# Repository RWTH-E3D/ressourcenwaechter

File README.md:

# Ressourcenwächter

*Resource Guardian - An open-source, modular Indoor Environmental Quality (IEQ) monitoring system featuring a gamified Graphical User Interface (GUI)*

**Resource Guardian's Wiki: [Link](https://rw.e3d.rwth-aachen.de/en/homepage-en/)**

## Overview

<!-- TOC -->
- [Ressourcenwächter](#ressourcenwächter)
  - [Overview](#overview)
  - [Key Features](#key-features)
  - [Design](#design)
  - [DIY Guide](#diy-guide)
  - [License](#license)
    - [Software \& Firmware](#software--firmware)
    - [Hardware](#hardware)
    - [Feedback System (Texts \& Concepts)](#feedback-system-texts--concepts)
    - [Documentation](#documentation)
    - [Artworks](#artworks)
  - [Acknowledgements](#acknowledgements)
  - [How to cite](#how-to-cite)
  - [Contributors](#contributors)
<!-- TOC -->

## Key Features

- **Modular IEQ monitoring system**

  Open-source system for monitoring key IEQ parameters, designed for real-world field studies and long-term deployment.

- **Multi-sensor data acquisition**

  Support for air temperature, humidity, illuminance, sound level, CO<sub>2</sub> concentration, VOC, wind speed, window status, electric power, and other IEQ sensors, with synchronized data collection and time-stamping.

- **Autonomous system**

  On-device GUI providing real-time visualization, intuitive interaction, and immediate feedback without requiring an external computer or internet connection. All data are stored locally on a microSD card.

- **Behavior-oriented feedback system**

  Context-aware feedback and recommendations aiming to support more resource-/energy-efficient and healthy user behavior, based on measured IEQ conditions.

<table>
<tr>
  <td align="center" valign="top">
      
      <br/>
      <sub><strong>Feedback System</strong><br/>Resource Guardian can provide recommendations and energy-saving tips based on your current IEQ environment</sub>
  </td>
  <td align="center" valign="top">
      
      <br/>
      <sub><strong>Sensor Data</strong><br/>Resource Guardian's modular design allows real-time IEQ data to be displayed based on your sensor configuration.</sub>
  </td>
</tr>
</table>

## Design

1. [Hardware](./hardware)
   1. [Enclosure](./hardware/enclosure)
   2. [PCB](./hardware/pcb)
2. [Microcontroller Firmware](./firmware)
3. [GUI](./software/gui)

## DIY Guide

- Step 1: [Prepare enclosure](https://rw.e3d.rwth-aachen.de/en/wiki/prepare-enclosure/)
- Step 2: [Prepare PCB](https://rw.e3d.rwth-aachen.de/en/wiki/prepare-pcb/)
- Step 3: [Assembling Resource Guardian](https://rw.e3d.rwth-aachen.de/en/wiki/assembling-ressourcenwaechter/)

## License

The *Ressourcenwächter (Resource Guardian)* project is a mixed open-source project consisting of software, firmware, hardware designs, documentation, feedback content, and third-party artwork. Different components of the project are released under different licenses, as outlined below.

In general, this project may be used, modified, and redistributed, provided that appropriate attribution is given and the respective license terms of each component are respected. **Non-commercial** use is permitted for all components, while commercial use is restricted for parts of the project licensed under non-commercial Creative Commons licenses. Third-party assets remain subject to their original licenses.

Please read this section carefully before reusing or redistributing any part of the project.

### Software & Firmware

The codebase is structured into following main components:

1. **Firmware:** Code running on embedded microcontrollers.

2. **Software for touch display GUI:** Graphical user interface running directly on the monitoring device.

<!-- 3. **Desktop software:** Desktop applications running on computers. -->

Author: Qirui Huang

License: GNU General Public License v3.0 (GPL-3.0)

Unless stated otherwise, all software and firmware developed within this project are licensed under GPL-3.0. Any derivative work must be distributed under the same license.

### Hardware

Author: Qirui Huang

License: Creative Commons Attribution-NonCommercial-ShareAlike
4.0 International (CC BY-NC-SA 4.0)

This license applies to all hardware-related materials, including but not limited to schematics, PCB layouts, enclosure designs, and mechanical drawings.

Commercial use is not permitted. Adaptations must be shared under the same
license.

### Feedback System (Texts & Concepts)

Authors: Qirui Huang, Marc Syndicus, Anna Langenbeck, Anna Deriks, Sonja Herzogenrath

License: CC BY-NC-SA 4.0

This license applies to feedback texts, categorization schemes, behavioral
recommendation concepts, and related content, except for quotations and otherwise indicated parts.

### Documentation

Authors: Qirui Huang, Marc Syndicus

License: CC BY-NC-SA 4.0

This includes assembly guides, methodological documentation, and other written materials, except for quotations and otherwise indicated parts.

### Artworks

This project incorporates third-party assets. These assets are not covered by the software license and remain subject to their respective licenses:

- [Dino Characters](https://arks.itch.io/dino-characters) by @[ArksDigital](https://x.com/ArksDigital), license: free
- [Dino Family](https://demching.itch.io/dino-family) by @[DemChing](https://demching.itch.io/), license: CC-BY 4.0
- [Sprout Lands Asset Pack](https://cupnooble.itch.io/sprout-lands-asset-pack) by @[Cup Nooble](https://cupnooble.itch.io/), license: free for non-commercial projects
- [Hearts](https://fliflifly.itch.io/hearts-and-health-bar) by @[fliflifly](https://fliflifly.itch.io/), license: CC-0

All artworks not listed above are created by Qirui Huang and licensed under
CC BY-NC-SA 4.0.

[Back to top ↥](#overview)

## Acknowledgements

The project Ressourcenwächter was funded by RWTH Aachen University's Sustainability Fund (Ref. 02-2023-004). We are grateful for the support.

[Back to top ↥](#overview)

## How to cite

If you use Resource Guardian in your academic work, please cite our journal paper: https://doi.org/10.1016/j.buildenv.2026.114657

  **Examples:**

  BibTeX:

  ```bibtex
  @article{Huang_2026_Potential_Gamification_BAE,
    title = {The potential of gamification in IEQ monitoring: Open-source hardware development and field studies},
    journal = {Building and Environment},
    volume = {298},
    pages = {114657},
    year = {2026},
    issn = {0360-1323},
    doi = {https://doi.org/10.1016/j.buildenv.2026.114657},
    url = {https://www.sciencedirect.com/science/article/pii/S0360132326004622},
    author = {Qirui Huang and Marc Syndicus and Dono Jamoliddinova and Jérôme Frisch and Christoph {van Treeck}},
    keywords = {Indoor environmental quality, Gamification, Monitoring, User behavior, Hardware},
  }
  ```

  APA style:
  ```
  Huang, Q., Syndicus, M., Jamoliddinova, D., Frisch, J., & van Treeck, C. (2026). The potential of gamification in IEQ monitoring: Open-source hardware development and field studies. Building and Environment, 298, 114657. https://doi.org/10.1016/j.buildenv.2026.114657
  ```

## Contributors

[Back to top ↥](#overview)

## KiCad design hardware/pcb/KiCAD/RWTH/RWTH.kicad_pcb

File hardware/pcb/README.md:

# Hardware Design

[DIY Guide: Prepare PCB](https://rw.e3d.rwth-aachen.de/en/wiki/prepare-pcb/)

## PCB

The relevant PCB documents can be found in this folder.

<br/>

We used [KiCAD](https://www.kicad.org/) for the design. To make DIY as easy as possible, we selected THT components instead of SMD.

Because there are no complex circuits and to reduce costs, we have chosen simple double-layer PCB, and the schematics for the top and bottom layers are shown below:

<br/>

<br/>

### Production files

You can give the latest version of the `.zip` file in the [production file folder](./output) (`./output`) to the PCB manufacturer for production.

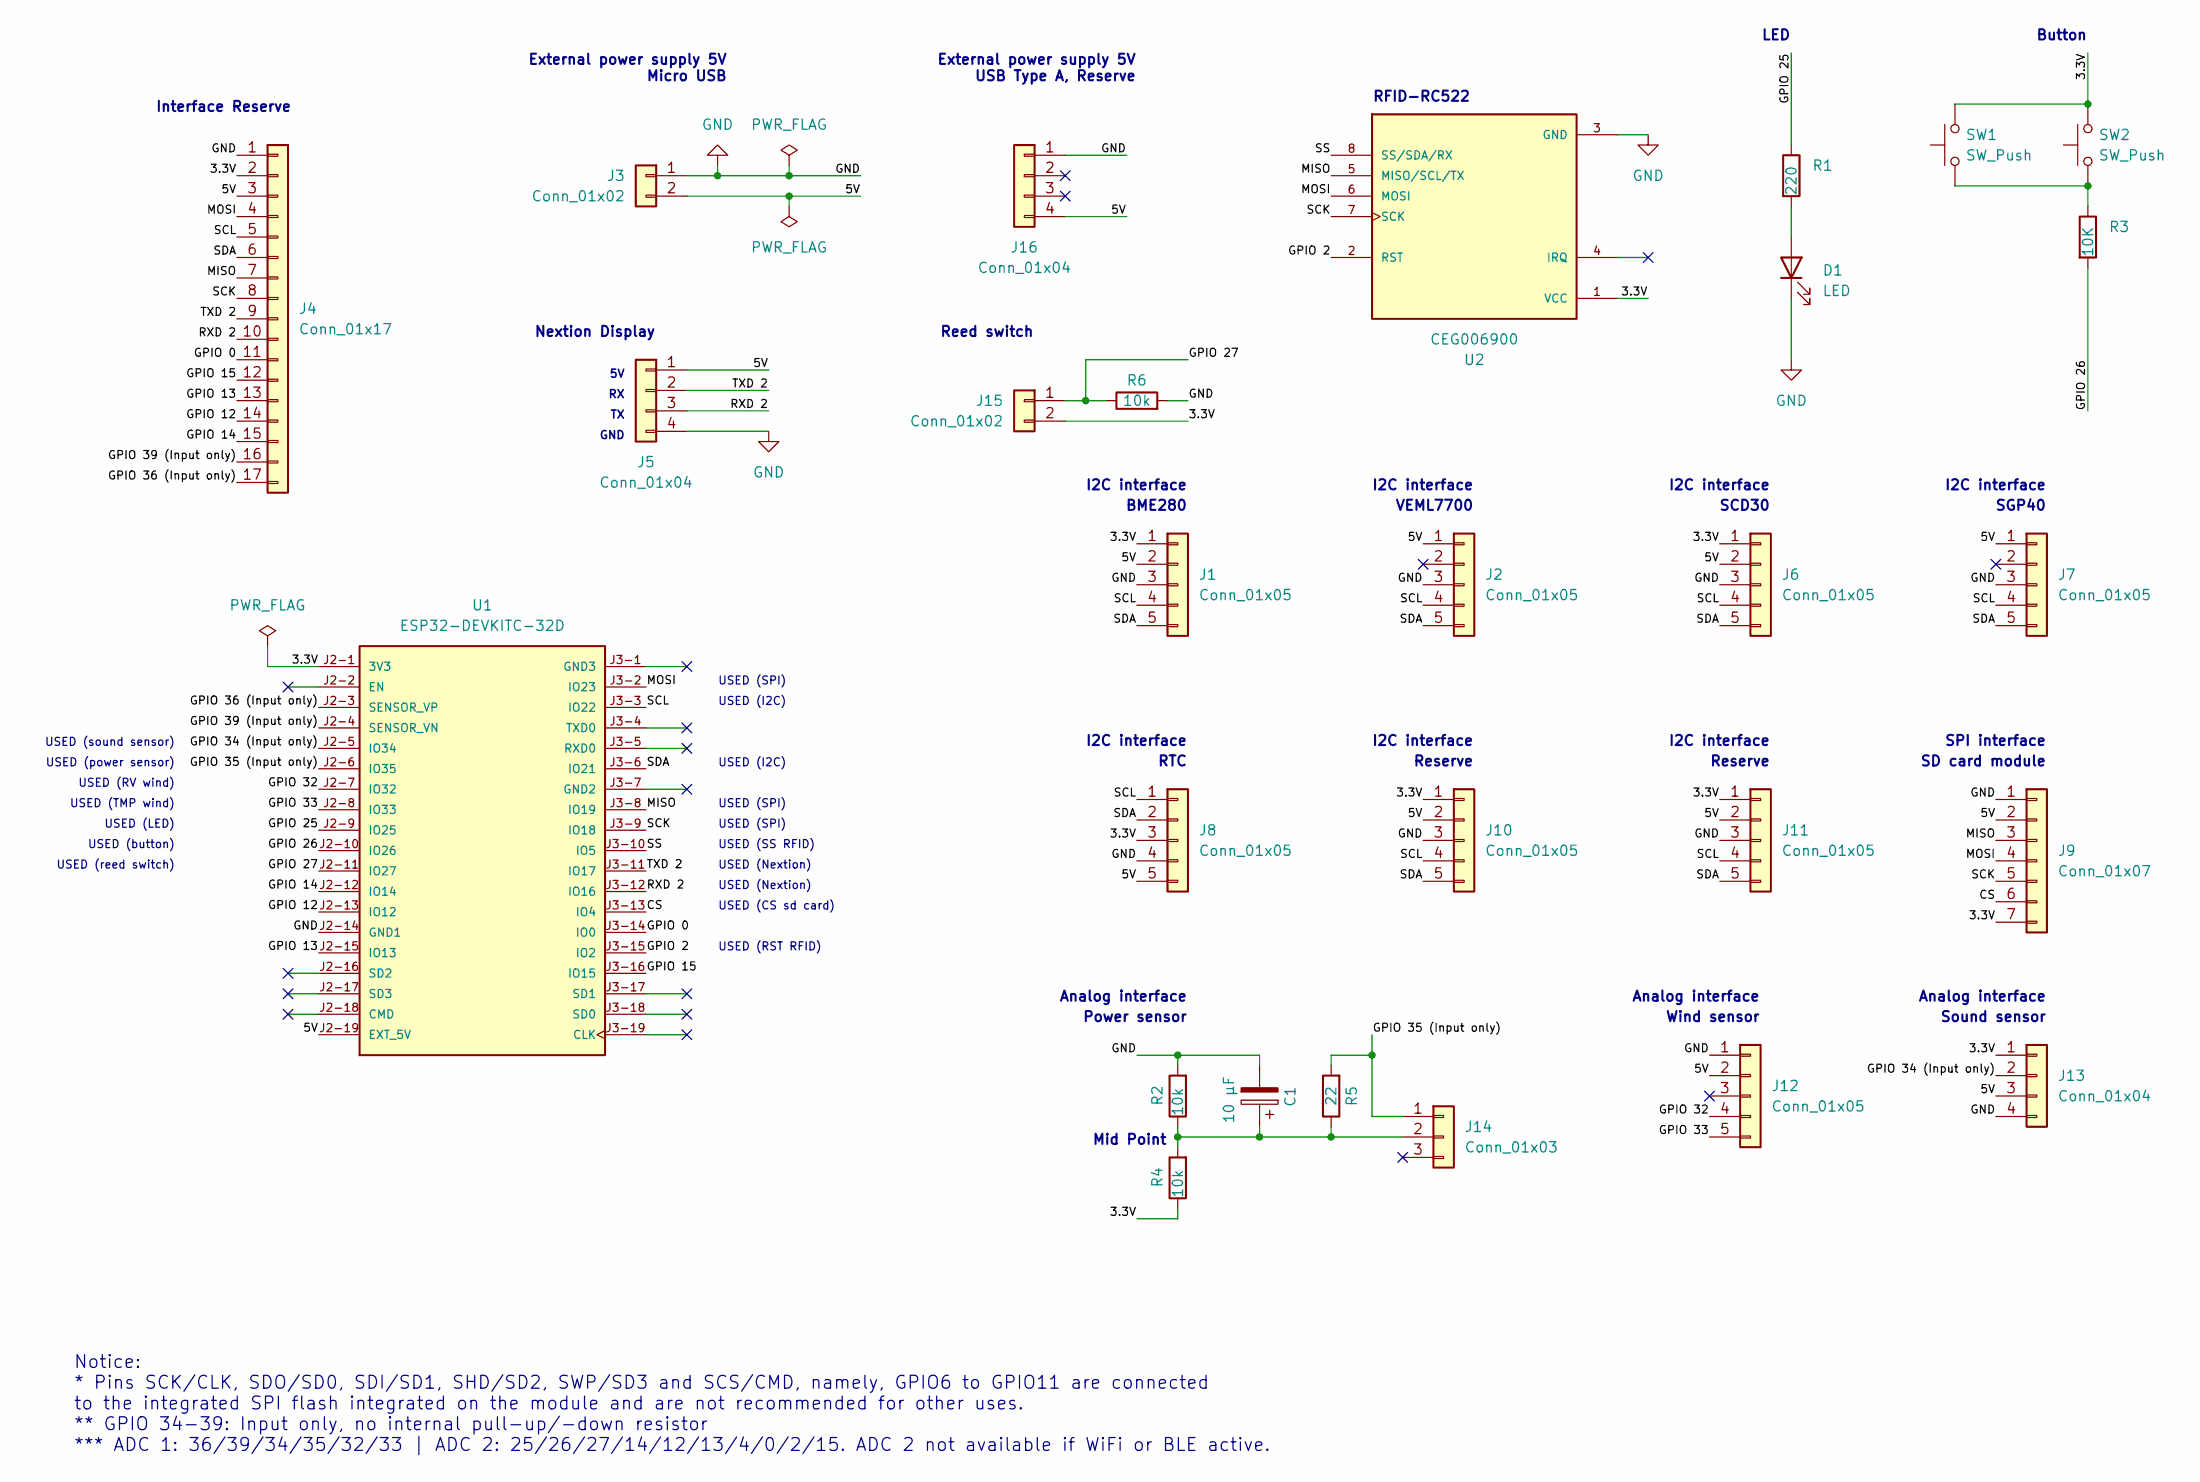
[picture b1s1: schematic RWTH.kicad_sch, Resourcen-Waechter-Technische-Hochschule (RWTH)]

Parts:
C1: 10 µF; CP_Radial_D5.0mm_P2.50mm
D1: LED; LED_D3.0mm
J1, J2, J6, J7, J8, J10, J11, J12: Conn_01x05; PinSocket_1x05_P2.54mm_Vertical
J3, J15: Conn_01x02; PinSocket_1x02_P2.54mm_Vertical
J4: Conn_01x17; PinSocket_1x17_P2.54mm_Vertical
J5, J13, J16: Conn_01x04; PinSocket_1x04_P2.54mm_Vertical
J9: Conn_01x07; PinSocket_1x07_P2.54mm_Vertical
J14: Conn_01x03; PinSocket_1x03_P2.54mm_Vertical
R1: 220; R_Axial_DIN0207_L6.3mm_D2.5mm_P10.16mm_Horizontal
R2, R4, R6: 10k; R_Axial_DIN0207_L6.3mm_D2.5mm_P10.16mm_Horizontal
R3: 10K; R_Axial_DIN0207_L6.3mm_D2.5mm_P10.16mm_Horizontal
R5: 22; R_Axial_DIN0207_L6.3mm_D2.5mm_P10.16mm_Horizontal
SW1: SW_Push; SW_Cherry_MX_1.00u_PCB
SW2: SW_Push; SW_PUSH_6mm_H9.5mm
U1: ESP32-DEVKITC-32D; MODULE_ESP32-DEVKITC-32D; PARTREV V4
U2: CEG006900; MODULE_CEG006900; PARTREV 12 June 2019

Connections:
/3.3V: J1.1, J4.2, J6.1, J8.3, J9.7, J10.1, J11.1, J13.1, J15.2, R4.1, SW1.2, SW2.2, U1.J2-1 (3V3), U2.1 (VCC)
/5V: J1.2, J2.1, J3.2, J4.3, J5.1, J6.2, J7.1, J8.5, J9.2, J10.2, J11.2, J12.2, J13.3, J16.4, U1.J2-19 (EXT_5V)
/CS: J9.6, U1.J3-13 (IO4)
/GPIO 0: J4.11, U1.J3-14 (IO0)
/GPIO 2: U1.J3-15 (IO2), U2.2 (RST)
/GPIO 12: J4.14, U1.J2-13 (IO12)
/GPIO 13: J4.13, U1.J2-15 (IO13)
/GPIO 14: J4.15, U1.J2-12 (IO14)
/GPIO 15: J4.12, U1.J3-16 (IO15)
/GPIO 25: R1.1, U1.J2-9 (IO25)
/GPIO 26: R3.2, U1.J2-10 (IO26)
/GPIO 27: J15.1, R6.1, U1.J2-11 (IO27)
/GPIO 32: J12.4, U1.J2-7 (IO32)
/GPIO 33: J12.5, U1.J2-8 (IO33)
/GPIO 34 (Input only): J13.2, U1.J2-5 (IO34)
/GPIO 35 (Input only): J14.1, R5.2, U1.J2-6 (IO35)
/GPIO 36 (Input only): J4.17, U1.J2-3 (SENSOR_VP)
/GPIO 39 (Input only): J4.16, U1.J2-4 (SENSOR_VN)
/MISO: J4.7, J9.3, U1.J3-8 (IO19), U2.5 (MISO/SCL/TX)
/MOSI: J4.4, J9.4, U1.J3-2 (IO23), U2.6 (MOSI)
/RXD 2: J4.10, J5.3, U1.J3-12 (IO16)
/SCK: J4.8, J9.5, U1.J3-9 (IO18), U2.7 (SCK)
/SCL: J1.4, J2.4, J4.5, J6.4, J7.4, J8.1, J10.4, J11.4, U1.J3-3 (IO22)
/SDA: J1.5, J2.5, J4.6, J6.5, J7.5, J8.2, J10.5, J11.5, U1.J3-6 (IO21)
/SS: U1.J3-10 (IO5), U2.8 (SS/SDA/RX)
/TXD 2: J4.9, J5.2, U1.J3-11 (IO17)
GND: C1.2, D1.1 (K), J1.3, J2.3, J3.1, J4.1, J5.4, J6.3, J7.3, J8.4, J9.1, J10.3, J11.3, J12.1, J13.4, J16.1, R2.2, R6.2, U1.J2-14 (GND1), U2.3 (GND)
unnamed: D1.2 (A), R1.2
unnamed: C1.1, J14.2, R2.1, R4.2, R5.1
unnamed: R3.1, SW1.1, SW2.1

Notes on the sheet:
Reed switch
I2C interface
USED (Nextion)
Analog interface
SD card module
SCD30
USED (sound sensor)
Power sensor
USED (LED)
LED
SGP40
SPI interface
Mid Point
Nextion Display
USED (I2C)
Wind sensor
USED (CS sd card)
USED (power sensor)
Reserve
USED (RV wind)
Sound sensor
USED (reed switch)
Notice: * Pins SCK/CLK, SDO/SD0, SDI/SD1, SHD/SD2, SWP/SD3 and SCS/CMD, namely, GPIO6 to GPIO11 are connected to the integrated SPI flash integrated on the module and are not recommended for other uses. ** GPIO 34-39: Input only, no internal pull-up/-down resistor *** ADC 1: 36/39/34/35/32/33 | ADC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
RFID-RC522
External power supply 5V Micro USB
RTC
VEML7700
External power supply 5V USB Type A, Reserve
USED (button)
BME280
Interface Reserve
USED (SPI)
Button
USED (SS RFID)
USED (TMP wind)
USED (RST RFID)
GND

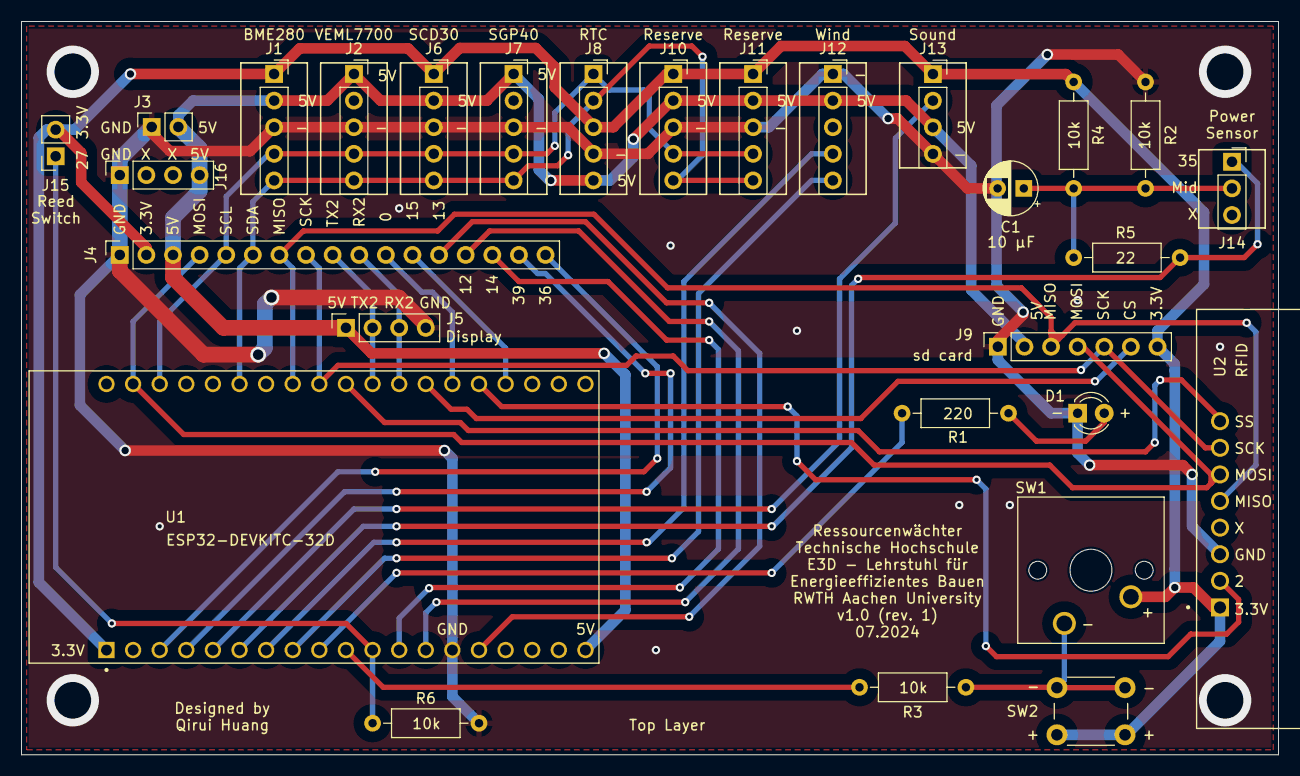
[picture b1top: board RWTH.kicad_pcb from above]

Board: 2 copper layers, 120.0 x 70.0 mm, 28 parts (0 on the bottom side), 30 nets.

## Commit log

2025-12-11 Add license
2025-12-16 Add funding info
2026-01-05 Upload hardware README
2026-01-05 Upload 3d printing files
2026-01-05 Upload enclosure models
2026-01-05 Upload PCB production files
2026-01-05 Upload PCB schematics
2026-04-23 upload source code
2026-04-23 upload KiCAD files
2026-04-23 Add citation
2026-06-09 Firmware v1.3.0: support Sensirion SCD4x CO2 sensors (SCD40/41)
